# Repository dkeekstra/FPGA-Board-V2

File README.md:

# FPGA Board V2
## Key Features:
* Intel Cyclone 10 
* 16k logic elements
* Onboard usb programmer
* 3x 2.5khz to 200MHz programmable clock
* 4Mb on board configuration memory
* 40pin GPIO header
* USB OTG and HDMI connector
* RS485
* 8x User leds
* 5x User push buttons
* 4x User dip switches

By D. Keekstra

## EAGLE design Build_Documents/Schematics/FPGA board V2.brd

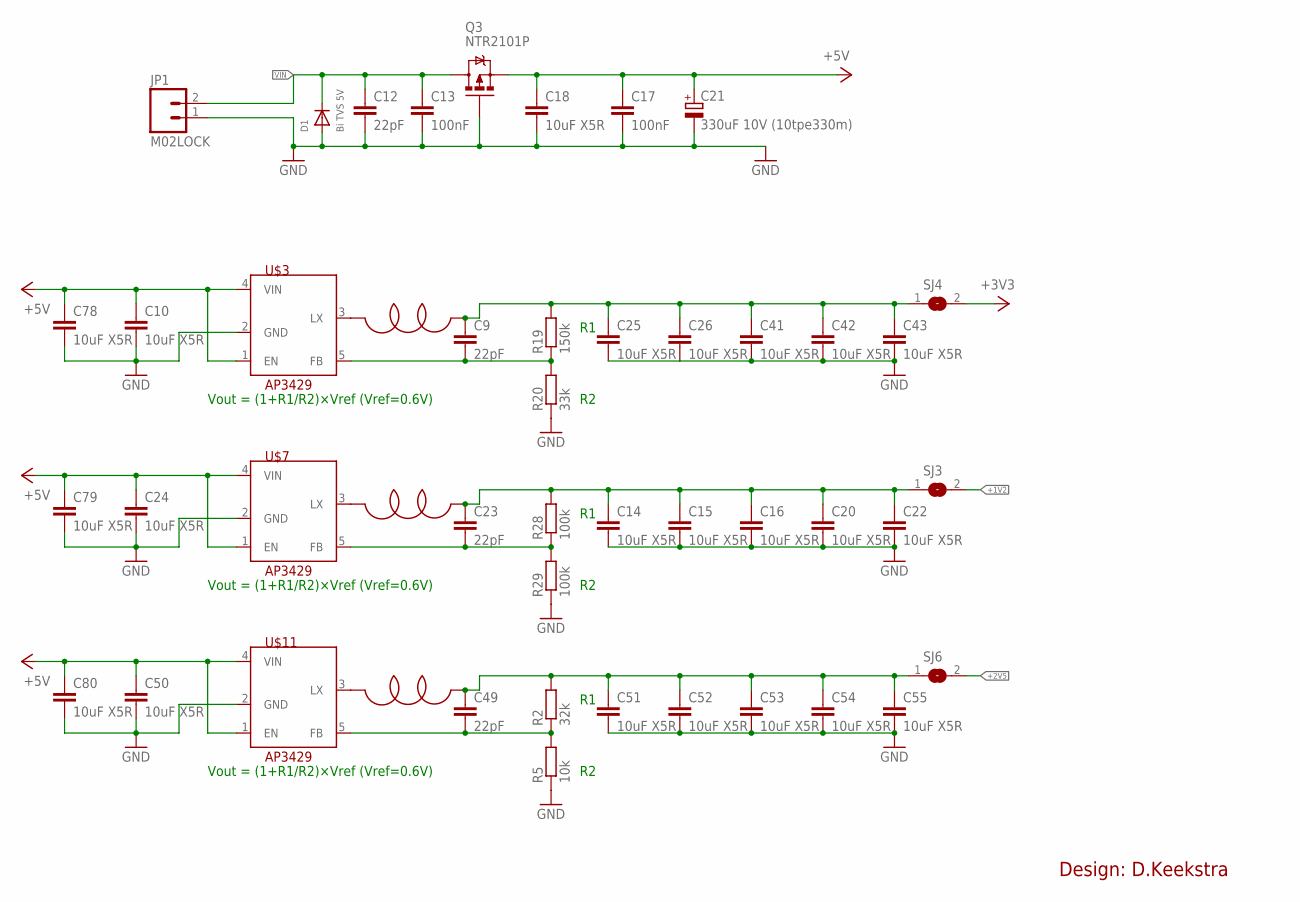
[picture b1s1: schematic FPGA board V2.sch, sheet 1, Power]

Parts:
C9, C12, C23, C49: 22pF; C0603
C10, C14, C15, C16, C18, C20, C22, C24, C25, C26, C41, C42, C43, C50, C51, C52, C53, C54, C55, C78, C79, C80: 10uF X5R; C0805K
C13, C17: 100nF; C0603
C21: 330uF 10V (10tpe330m); D/7343-31W
D1: Bi TVS 5V; SOD-523
JP1: M02LOCK; 1X02_LOCK
L2, L3, L4: 3.3uH 1.9A PWR; SLF7032T
Q3: NTR2101P; SOT23-3
R2: 32k; R0603
R5: 10k; R0603
R19: 150k; R0603
R20: 33k; R0603
R28, R29: 100k; R0603
SJ3, SJ4, SJ6: SJ
U$3, U$7, U$11: AP3429; TSOT-25

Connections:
+1V2: SJ3.2; also elsewhere on the board
+2V5: SJ6.2; also elsewhere on the board
+3V3: SJ4.2; also elsewhere on the board
+5V: C10.1, C17.1, C18.1, C21.+, C24.1, C50.1, C78.1, C79.1, C80.1, Q3.2 (S), U$3.1 (EN), U$3.4 (VIN), U$7.1 (EN), U$7.4 (VIN), U$11.1 (EN), U$11.4 (VIN); also elsewhere on the board
GND: C10.2, C12.2, C13.2, C14.2, C15.2, C16.2, C17.2, C18.2, C20.2, C21.-, C22.2, C24.2, C25.2, C26.2, C41.2, C42.2, C43.2, C50.2, C51.2, C52.2, C53.2, C54.2, C55.2, C78.2, C79.2, C80.2, D1.A, JP1.1, Q3.1 (G), R5.1, R20.1, R29.1, U$3.2 (GND), U$7.2 (GND), U$11.2 (GND); also elsewhere on the board
L2: C9.1, C25.1, C26.1, C41.1, C42.1, C43.1, L2.P$1, R19.2, SJ4.1
unnamed: L3.P$2, U$11.3 (LX)
unnamed: C49.1, C51.1, C52.1, C53.1, C54.1, C55.1, L3.P$1, R2.2, SJ6.1
unnamed: C49.2, R2.1, R5.2, U$11.5 (FB)
unnamed: C14.1, C15.1, C16.1, C20.1, C22.1, C23.1, L4.P$1, R28.2, SJ3.1
unnamed: C23.2, R28.1, R29.2, U$7.5 (FB)
unnamed: L2.P$2, U$3.3 (LX)
unnamed: C9.2, R19.1, R20.2, U$3.5 (FB)
unnamed: L4.P$2, U$7.3 (LX)
VIN: C12.1, C13.1, D1.K (C), JP1.2, Q3.3 (D); also elsewhere on the board

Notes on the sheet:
Vout = (1+R1/R2)×Vref (Vref=0.6V)
Design: D.Keekstra

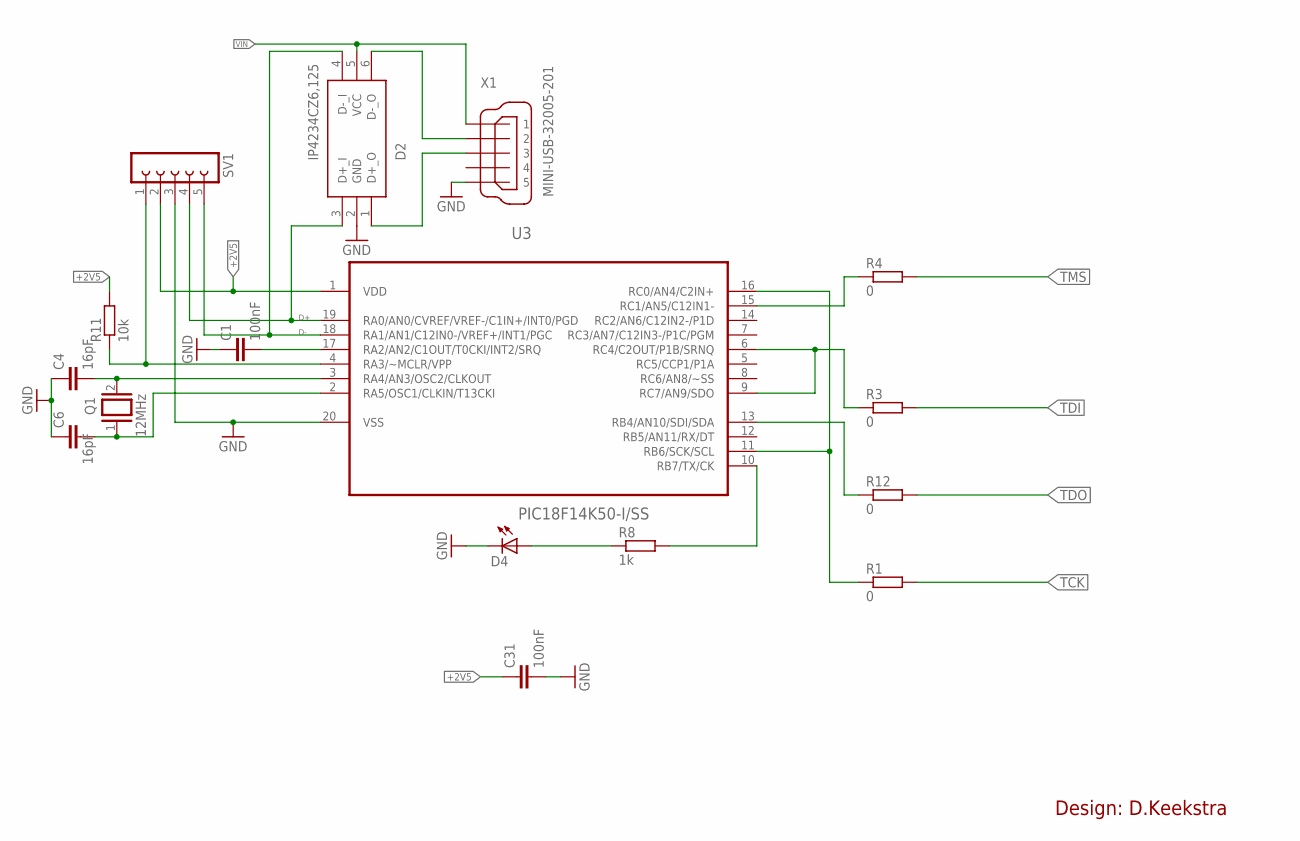
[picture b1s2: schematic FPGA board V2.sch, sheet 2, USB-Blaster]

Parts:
C1, C31: 100nF; C0603
C4, C6: 16pF; C0603
D2: IP4234CZ6,125; SOT95P275X110-6N
D4: LED0805; CHIPLED_0805
Q1: 12MHz; QS
R1, R3, R4, R12: 0; R0603
R8: 1k; R0603
R11: 10k; R0603
SV1: FE05-1
U3: PIC18F14K50-I/SS; SOP65P780X200-20N
X1: MINI-USB-32005-201; 32005-201

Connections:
+2V5: C31.1, R11.2, SV1.2, U3.1 (VDD); also elsewhere on the board
D+: D2.3 (D+_I), SV1.4, U3.19 (RA0/AN0/CVREF/VREF-/C1IN+/INT0/PGD)
D-: D2.4 (D-_I), SV1.5, U3.18 (RA1/AN1/C12IN0-/VREF+/INT1/PGC)
GND: C1.1, C4.1, C6.1, C31.2, D2.2 (GND), D4.C, SV1.3, U3.20 (VSS), X1.5; also elsewhere on the board
unnamed: R8.2, U3.10 (RB7/TX/CK)
unnamed: D4.A, R8.1
unnamed: R1.1, U3.11 (RB6/SCK/SCL), U3.16 (RC0/AN4/C2IN+)
unnamed: C1.2, U3.17 (RA2/AN2/C1OUT/T0CKI/INT2/SRQ)
unnamed: R4.1, U3.15 (RC1/AN5/C12IN1-)
unnamed: R11.1, SV1.1, U3.4 (RA3/~MCLR/VPP)
unnamed: R3.1, U3.6 (RC4/C2OUT/P1B/SRNQ), U3.9 (RC7/AN9/SDO)
unnamed: D2.1 (D+_O), X1.3
unnamed: R12.1, U3.13 (RB4/AN10/SDI/SDA)
unnamed: D2.6 (D-_O), X1.2
unnamed: C4.2, Q1.2, U3.3 (RA4/AN3/OSC2/CLKOUT)
unnamed: C6.2, Q1.1, U3.2 (RA5/OSC1/CLKIN/T13CKI)
TCK: R1.2; also elsewhere on the board
TDI: R3.2; also elsewhere on the board
TDO: R12.2; also elsewhere on the board
TMS: R4.2; also elsewhere on the board
VIN: D2.5 (VCC), X1.1; also elsewhere on the board

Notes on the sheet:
Design: D.Keekstra

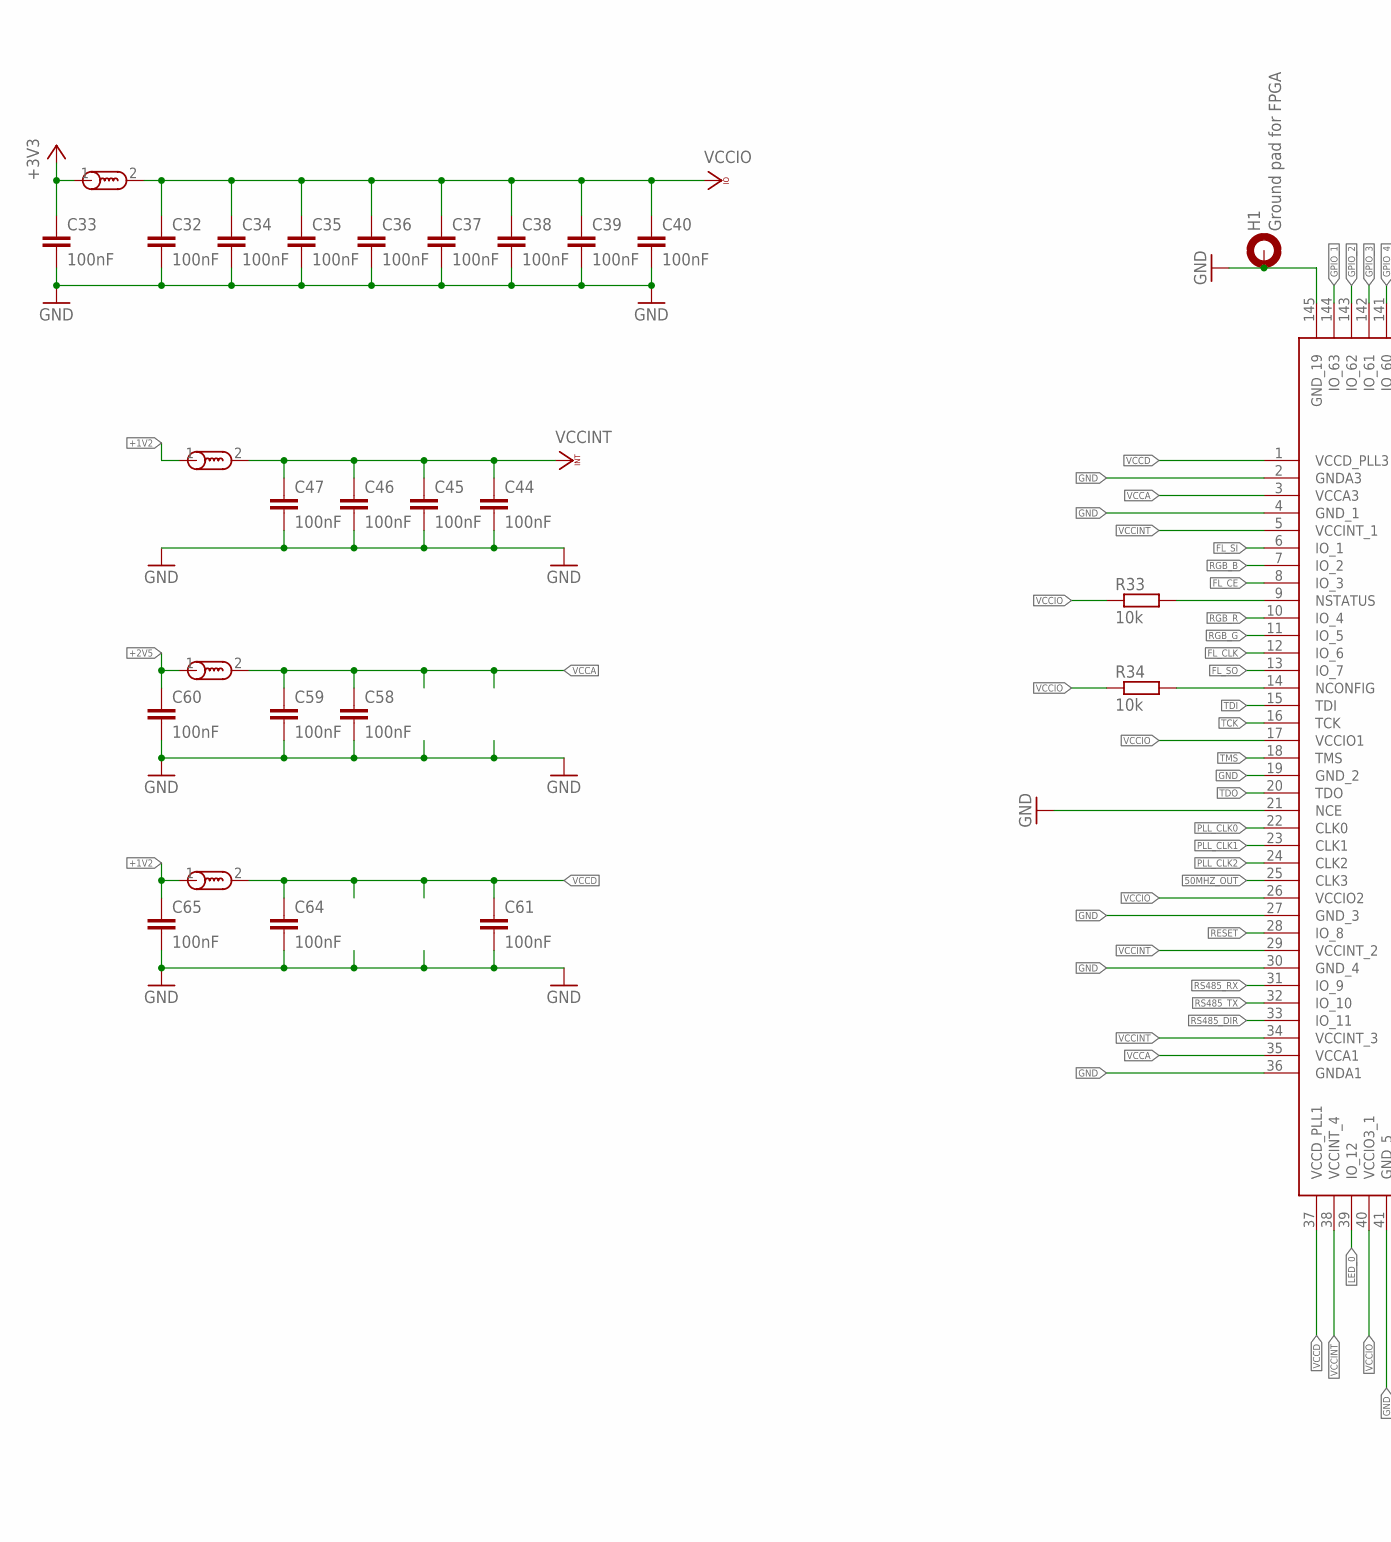
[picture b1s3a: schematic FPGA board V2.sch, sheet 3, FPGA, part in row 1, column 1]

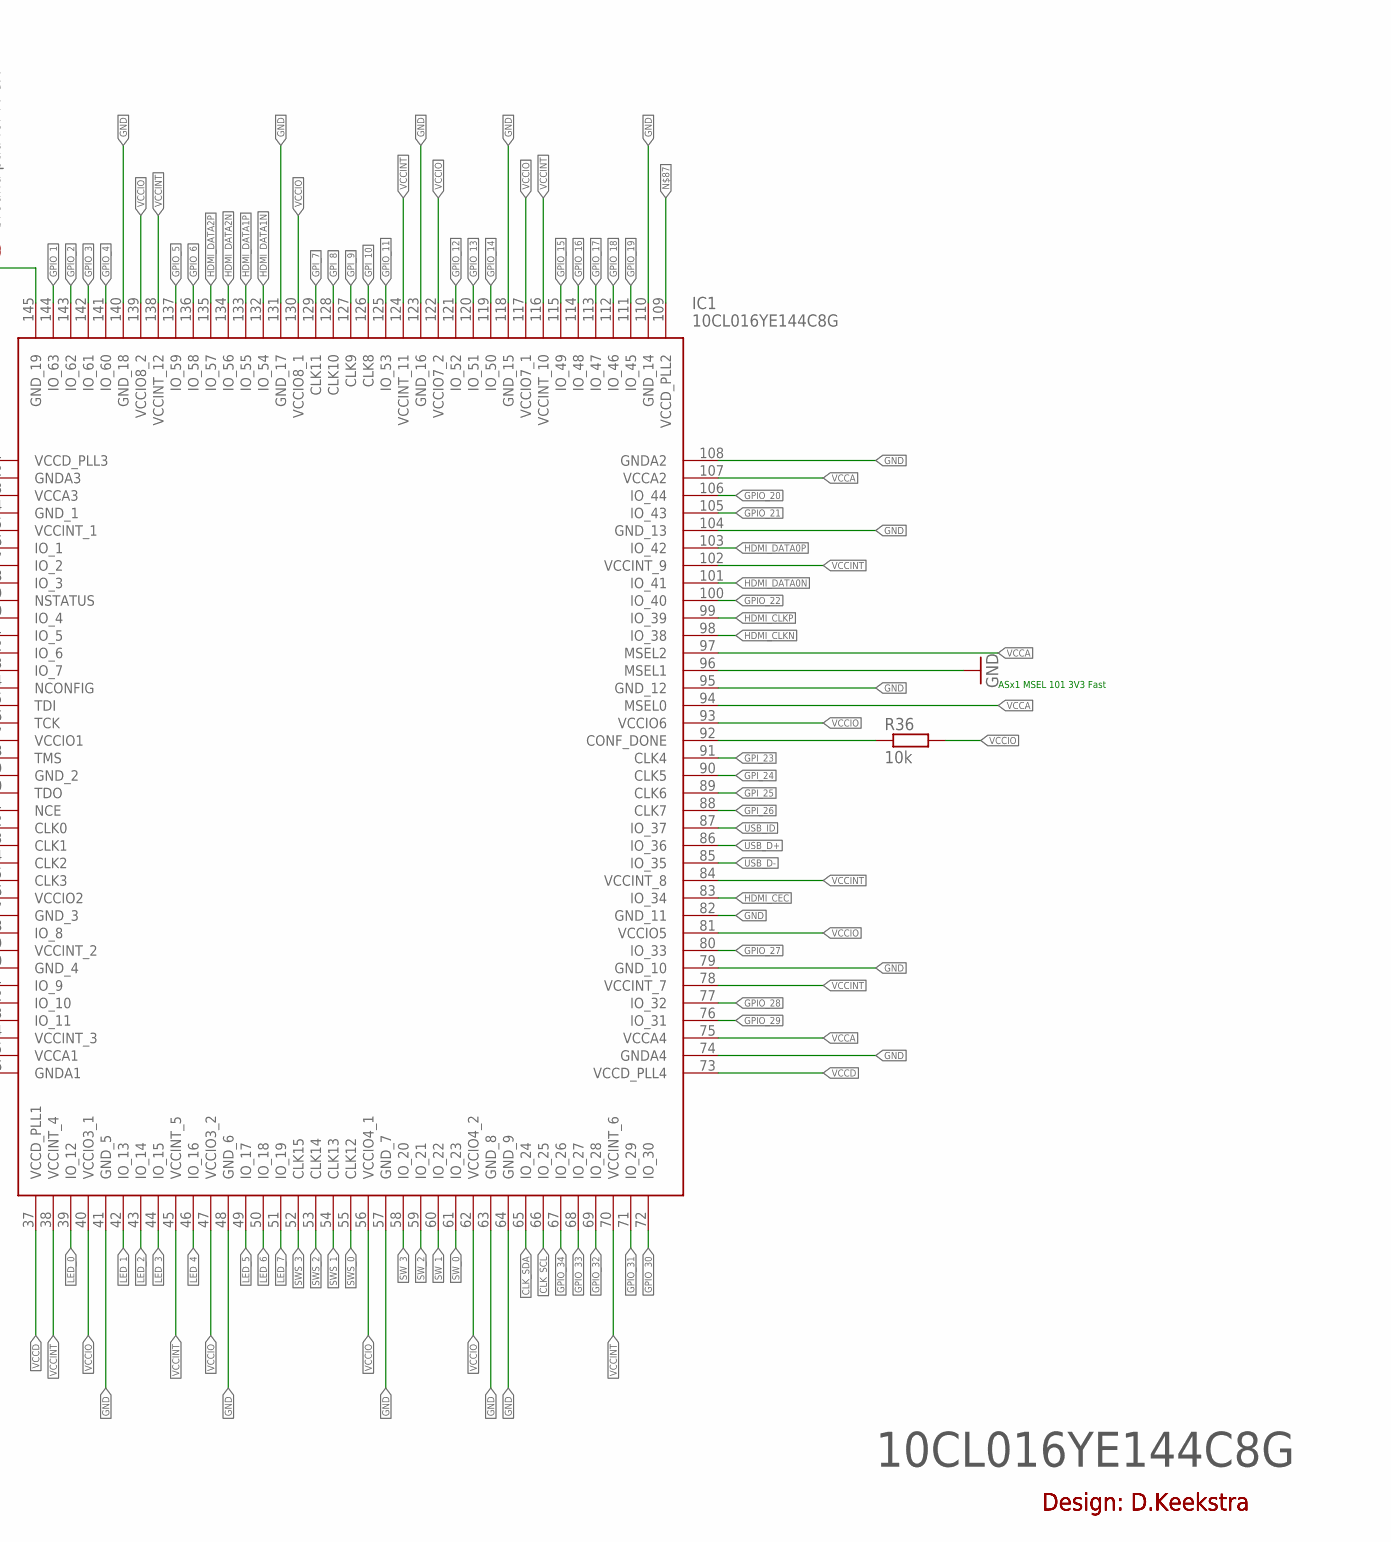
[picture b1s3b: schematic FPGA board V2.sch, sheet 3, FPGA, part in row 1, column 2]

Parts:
B1, B2, B3, B4: B-EU; C0603
C32, C33, C34, C35, C36, C37, C38, C39, C40, C44, C45, C46, C47, C58, C59, C60, C61, C64, C65: 100nF; C0603
H1: Ground pad for FPGA; 2,8-PAD
IC1: 10CL016YE144C8G; QFP50P2200X2200X165-145N
R33, R34, R36: 10k; R0603

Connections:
50MHZ_OUT: IC1.25 (CLK3); also elsewhere on the board
+1V2: B2.1, B4.1, C65.1; also elsewhere on the board
+2V5: B3.1, C60.1; also elsewhere on the board
+3V3: B1.1, C33.1; also elsewhere on the board
CLK_SCL: IC1.66 (IO_25); also elsewhere on the board
CLK_SDA: IC1.65 (IO_24); also elsewhere on the board
FL_CE: IC1.8 (IO_3); also elsewhere on the board
FL_CLK: IC1.12 (IO_6); also elsewhere on the board
FL_SI: IC1.6 (IO_1); also elsewhere on the board
FL_SO: IC1.13 (IO_7); also elsewhere on the board
GND: C32.2, C33.2, C34.2, C35.2, C36.2, C37.2, C38.2, C39.2, C40.2, C44.2, C45.2, C46.2, C47.2, C58.2, C59.2, C60.2, C61.2, C64.2, C65.2, H1.B2,8, IC1.2 (GNDA3), IC1.4 (GND_1), IC1.19 (GND_2), IC1.21 (NCE), IC1.27 (GND_3), IC1.30 (GND_4), IC1.36 (GNDA1), IC1.41 (GND_5), IC1.48 (GND_6), IC1.57 (GND_7), IC1.63 (GND_8), IC1.64 (GND_9), IC1.74 (GNDA4), IC1.79 (GND_10), IC1.82 (GND_11), IC1.95 (GND_12), IC1.96 (MSEL1), IC1.104 (GND_13), IC1.108 (GNDA2), IC1.110 (GND_14), IC1.118 (GND_15), IC1.123 (GND_16), IC1.131 (GND_17), IC1.140 (GND_18), IC1.145 (GND_19); also elsewhere on the board
GPIO_1: IC1.144 (IO_63); also elsewhere on the board
GPIO_2: IC1.143 (IO_62); also elsewhere on the board
GPIO_3: IC1.142 (IO_61); also elsewhere on the board
GPIO_4: IC1.141 (IO_60); also elsewhere on the board
GPIO_5: IC1.137 (IO_59); also elsewhere on the board
GPIO_6: IC1.136 (IO_58); also elsewhere on the board
GPIO_11: IC1.125 (IO_53); also elsewhere on the board
GPIO_12: IC1.121 (IO_52); also elsewhere on the board
GPIO_13: IC1.120 (IO_51); also elsewhere on the board
GPIO_14: IC1.119 (IO_50); also elsewhere on the board
GPIO_15: IC1.115 (IO_49); also elsewhere on the board
GPIO_16: IC1.114 (IO_48); also elsewhere on the board
GPIO_17: IC1.113 (IO_47); also elsewhere on the board
GPIO_18: IC1.112 (IO_46); also elsewhere on the board
GPIO_19: IC1.111 (IO_45); also elsewhere on the board
GPIO_20: IC1.106 (IO_44); also elsewhere on the board
GPIO_21: IC1.105 (IO_43); also elsewhere on the board
GPIO_22: IC1.100 (IO_40); also elsewhere on the board
GPIO_27: IC1.80 (IO_33); also elsewhere on the board
GPIO_28: IC1.77 (IO_32); also elsewhere on the board
GPIO_29: IC1.76 (IO_31); also elsewhere on the board
GPIO_30: IC1.72 (IO_30); also elsewhere on the board
GPIO_31: IC1.71 (IO_29); also elsewhere on the board
GPIO_32: IC1.69 (IO_28); also elsewhere on the board
GPIO_33: IC1.68 (IO_27); also elsewhere on the board
GPIO_34: IC1.67 (IO_26); also elsewhere on the board
GPI_7: IC1.129 (CLK11); also elsewhere on the board
GPI_8: IC1.128 (CLK10); also elsewhere on the board
GPI_9: IC1.127 (CLK9); also elsewhere on the board
GPI_10: IC1.126 (CLK8); also elsewhere on the board
GPI_23: IC1.91 (CLK4); also elsewhere on the board
GPI_24: IC1.90 (CLK5); also elsewhere on the board
GPI_25: IC1.89 (CLK6); also elsewhere on the board
GPI_26: IC1.88 (CLK7); also elsewhere on the board
HDMI_CEC: IC1.83 (IO_34); also elsewhere on the board
HDMI_CLKN: IC1.98 (IO_38); also elsewhere on the board
HDMI_CLKP: IC1.99 (IO_39); also elsewhere on the board
HDMI_DATA0N: IC1.101 (IO_41); also elsewhere on the board
HDMI_DATA0P: IC1.103 (IO_42); also elsewhere on the board
HDMI_DATA1N: IC1.132 (IO_54); also elsewhere on the board
HDMI_DATA1P: IC1.133 (IO_55); also elsewhere on the board
HDMI_DATA2N: IC1.134 (IO_56); also elsewhere on the board
HDMI_DATA2P: IC1.135 (IO_57); also elsewhere on the board
LED_0: IC1.39 (IO_12); also elsewhere on the board
LED_1: IC1.42 (IO_13); also elsewhere on the board
LED_2: IC1.43 (IO_14); also elsewhere on the board
LED_3: IC1.44 (IO_15); also elsewhere on the board
LED_4: IC1.46 (IO_16); also elsewhere on the board
LED_5: IC1.49 (IO_17); also elsewhere on the board
LED_6: IC1.50 (IO_18); also elsewhere on the board
LED_7: IC1.51 (IO_19); also elsewhere on the board
unnamed: IC1.9 (NSTATUS), R33.2
unnamed: IC1.14 (NCONFIG), R34.2
unnamed: IC1.92 (CONF_DONE), R36.1
PLL_CLK0: IC1.22 (CLK0); also elsewhere on the board
PLL_CLK1: IC1.23 (CLK1); also elsewhere on the board
PLL_CLK2: IC1.24 (CLK2); also elsewhere on the board
RESET: IC1.28 (IO_8); also elsewhere on the board
RGB_B: IC1.7 (IO_2); also elsewhere on the board
RGB_G: IC1.11 (IO_5); also elsewhere on the board
RGB_R: IC1.10 (IO_4); also elsewhere on the board
RS485_DIR: IC1.33 (IO_11); also elsewhere on the board
RS485_RX: IC1.31 (IO_9); also elsewhere on the board
RS485_TX: IC1.32 (IO_10); also elsewhere on the board
SWS_0: IC1.55 (CLK12); also elsewhere on the board
SWS_1: IC1.54 (CLK13); also elsewhere on the board
SWS_2: IC1.53 (CLK14); also elsewhere on the board
SWS_3: IC1.52 (CLK15); also elsewhere on the board
SW_0: IC1.61 (IO_23); also elsewhere on the board
SW_1: IC1.60 (IO_22); also elsewhere on the board
SW_2: IC1.59 (IO_21); also elsewhere on the board
SW_3: IC1.58 (IO_20); also elsewhere on the board
TCK: IC1.16 (TCK); also elsewhere on the board
TDI: IC1.15 (TDI); also elsewhere on the board
TDO: IC1.20 (TDO); also elsewhere on the board
TMS: IC1.18 (TMS); also elsewhere on the board
USB_D+: IC1.86 (IO_36); also elsewhere on the board
USB_D-: IC1.85 (IO_35); also elsewhere on the board
USB_ID: IC1.87 (IO_37); also elsewhere on the board
VCCA: B3.2, C58.1, C59.1, IC1.3 (VCCA3), IC1.35 (VCCA1), IC1.75 (VCCA4), IC1.94 (MSEL0), IC1.97 (MSEL2), IC1.107 (VCCA2)
VCCD: B4.2, C61.1, C64.1, IC1.1 (VCCD_PLL3), IC1.37 (VCCD_PLL1), IC1.73 (VCCD_PLL4)
VCCINT: B2.2, C44.1, C45.1, C46.1, C47.1, IC1.5 (VCCINT_1), IC1.29 (VCCINT_2), IC1.34 (VCCINT_3), IC1.38 (VCCINT_4), IC1.45 (VCCINT_5), IC1.70 (VCCINT_6), IC1.78 (VCCINT_7), IC1.84 (VCCINT_8), IC1.102 (VCCINT_9), IC1.116 (VCCINT_10), IC1.124 (VCCINT_11), IC1.138 (VCCINT_12)
VCCIO: B1.2, C32.1, C34.1, C35.1, C36.1, C37.1, C38.1, C39.1, C40.1, IC1.17 (VCCIO1), IC1.26 (VCCIO2), IC1.40 (VCCIO3_1), IC1.47 (VCCIO3_2), IC1.56 (VCCIO4_1), IC1.62 (VCCIO4_2), IC1.81 (VCCIO5), IC1.93 (VCCIO6), IC1.117 (VCCIO7_1), IC1.122 (VCCIO7_2), IC1.130 (VCCIO8_1), IC1.139 (VCCIO8_2), R33.1, R34.1, R36.2

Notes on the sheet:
10CL016YE144C8G
ASx1 MSEL 101 3V3 Fast
Design: D.Keekstra

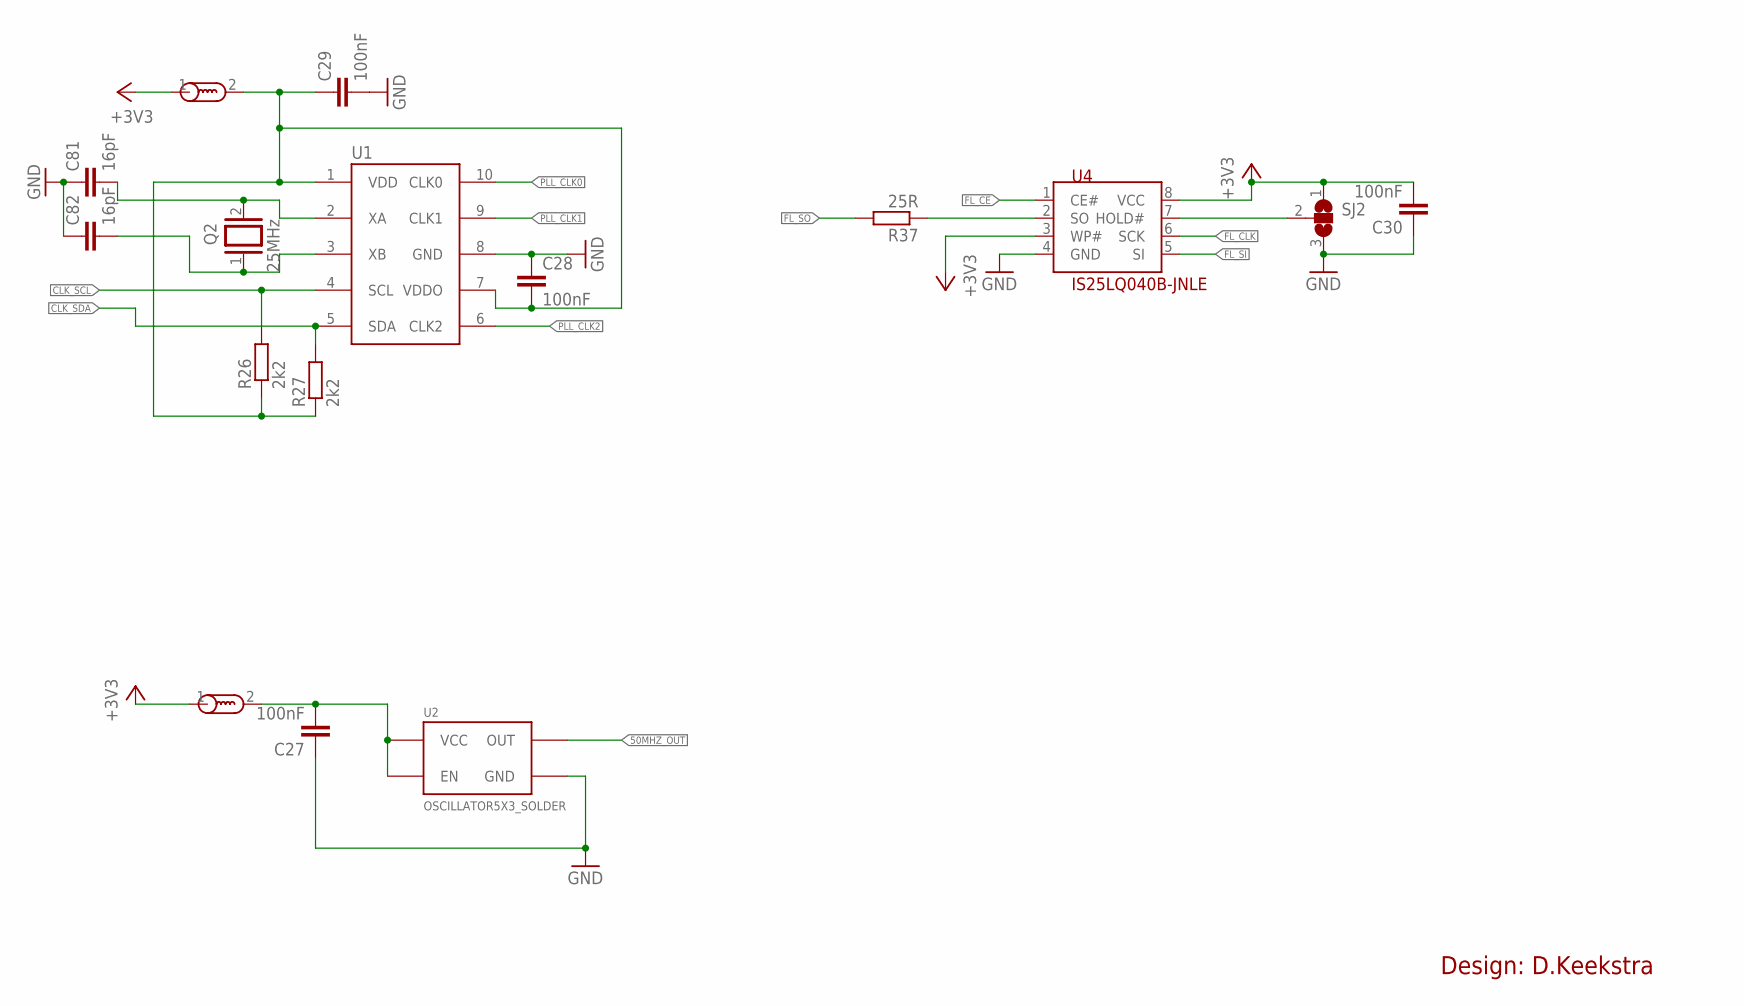
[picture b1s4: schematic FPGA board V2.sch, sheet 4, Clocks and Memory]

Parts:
B5, B6: B-EU; C0603
C27, C28, C29, C30: 100nF; C0603
C81, C82: 16pF; C0603
Q2: 25MHz; QS
R26, R27: 2k2; R0603
R37: 25R; R0603
SJ2: SJ2W; SJ_2
U1: SI5351A_CLOCK_GEN; MSOP-10
U2: OSCILLATOR5X3_SOLDER; CRYSTAL-SMD-5X3_SOLDER
U4: IS25LQ040B-JNLE; SOIC8

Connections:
50MHZ_OUT: U2.3 (OUT); also elsewhere on the board
+3V3: B5.1, B6.1, C30.2, SJ2.1, U4.3 (WP#), U4.8 (VCC); also elsewhere on the board
CLK_SCL: R26.2, U1.4 (SCL); also elsewhere on the board
CLK_SDA: R27.2, U1.5 (SDA); also elsewhere on the board
FL_CE: U4.1 (CE#); also elsewhere on the board
FL_CLK: U4.6 (SCK); also elsewhere on the board
FL_SI: U4.5 (SI); also elsewhere on the board
FL_SO: R37.2; also elsewhere on the board
GND: C27.1, C28.1, C29.2, C30.1, C81.1, C82.1, SJ2.3, U1.8 (GND), U2.2 (GND), U4.4 (GND); also elsewhere on the board
unnamed: C82.2, Q2.1, U1.3 (XB)
unnamed: C81.2, Q2.2, U1.2 (XA)
unnamed: SJ2.2, U4.7 (HOLD#)
unnamed: B6.2, C28.2, C29.1, R26.1, R27.1, U1.1 (VDD), U1.7 (VDDO)
unnamed: B5.2, C27.2, U2.1 (EN), U2.4 (VCC)
PLL_CLK0: U1.10 (CLK0); also elsewhere on the board
PLL_CLK1: U1.9 (CLK1); also elsewhere on the board
PLL_CLK2: U1.6 (CLK2); also elsewhere on the board
SO: R37.1, U4.2 (SO)

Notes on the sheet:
Design: D.Keekstra

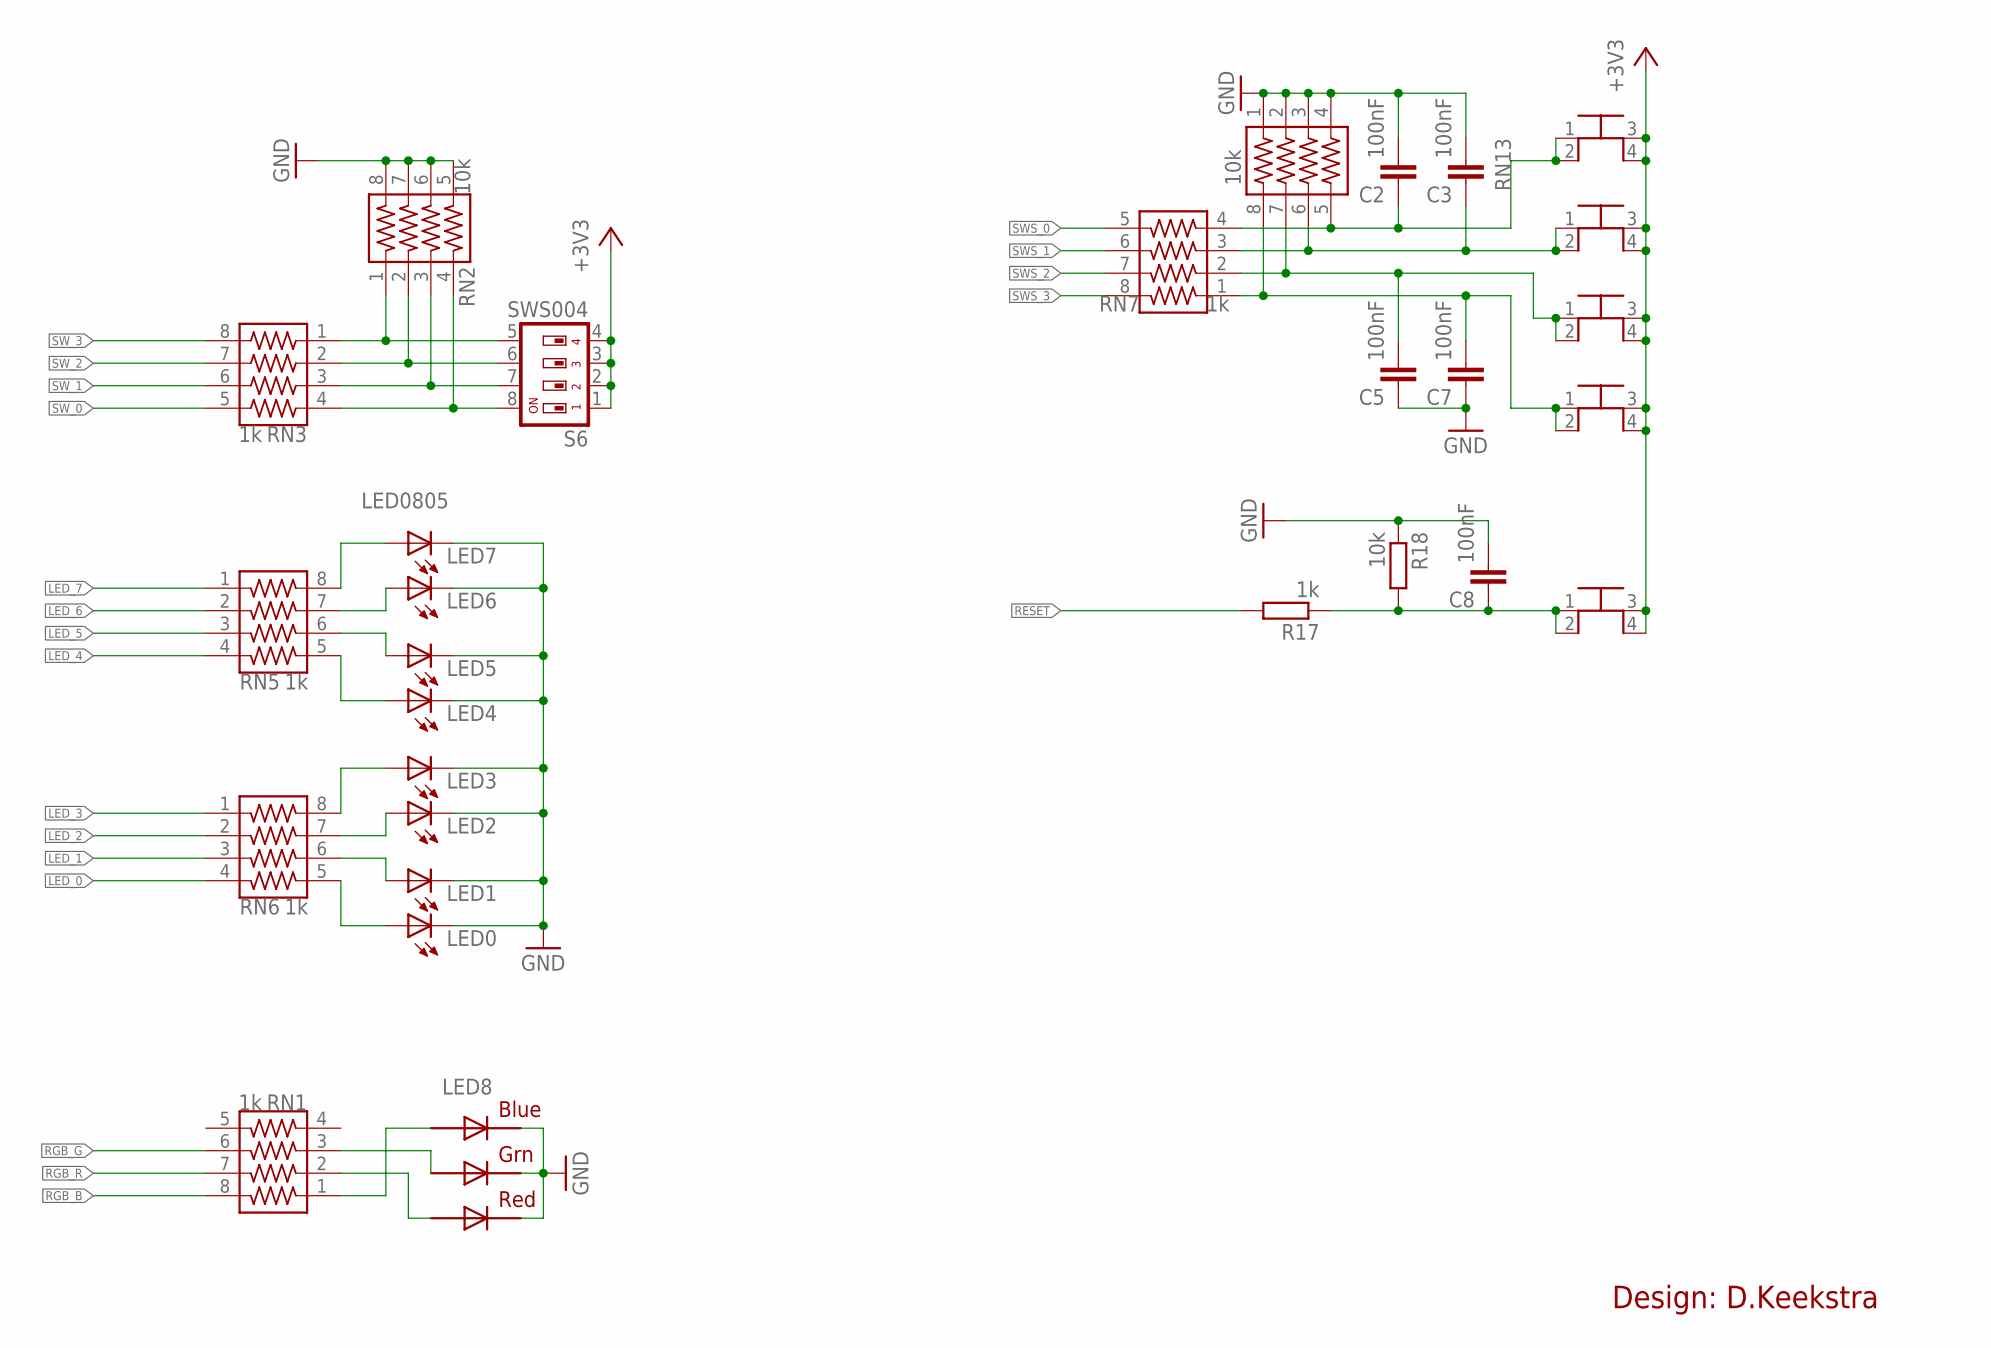
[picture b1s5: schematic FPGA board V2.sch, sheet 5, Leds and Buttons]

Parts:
C2, C3, C5, C7, C8: 100nF; C0603
LED0, LED1, LED2, LED3, LED4, LED5, LED6, LED7: LED0805; CHIPLED_0805
LED8: RGBLED5050
R17: 1k; R0603
R18: 10k; R0603
RN1, RN3, RN5, RN6, RN7: 1k; 744-8NS
RN2, RN13: 10k; 744-8NS
S1, S2, S3, S4, S5: SKQGADE010; SKQGAKE010
S6: SWS004; SMS-004

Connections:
+3V3: S1.3, S1.4, S2.3, S2.4, S3.3, S3.4, S4.3, S4.4, S5.3, S5.4, S6.1, S6.2, S6.3, S6.4; also elsewhere on the board
GND: C2.2, C3.2, C5.1, C7.1, C8.2, LED0.C, LED1.C, LED2.C, LED3.C, LED4.C, LED5.C, LED6.C, LED7.C, LED8.4 (BLUE_C), LED8.5 (RED_C), LED8.6 (GREEN_C), R18.1, RN2.5, RN2.6, RN2.7, RN2.8, RN13.1, RN13.2, RN13.3, RN13.4; also elsewhere on the board
LED_0: RN6.4; also elsewhere on the board
LED_1: RN6.3; also elsewhere on the board
LED_2: RN6.2; also elsewhere on the board
LED_3: RN6.1; also elsewhere on the board
LED_4: RN5.4; also elsewhere on the board
LED_5: RN5.3; also elsewhere on the board
LED_6: RN5.2; also elsewhere on the board
LED_7: RN5.1; also elsewhere on the board
unnamed: RN2.3, RN3.3, S6.7
unnamed: RN2.1, RN3.1, S6.5
unnamed: RN2.2, RN3.2, S6.6
unnamed: RN2.4, RN3.4, S6.8
unnamed: LED7.A, RN5.8
unnamed: LED6.A, RN5.7
unnamed: LED5.A, RN5.6
unnamed: LED4.A, RN5.5
unnamed: LED3.A, RN6.8
unnamed: LED2.A, RN6.7
unnamed: LED1.A, RN6.6
unnamed: LED0.A, RN6.5
unnamed: LED8.1 (GREEN_A), RN1.3
unnamed: LED8.2 (RED_A), RN1.2
unnamed: LED8.3 (BLUE_A), RN1.1
unnamed: C2.1, RN7.4, RN13.5, S4.1, S4.2
unnamed: C3.1, RN7.3, RN13.6, S3.1, S3.2
unnamed: C5.2, RN7.2, RN13.7, S2.1, S2.2
unnamed: C7.2, RN7.1, RN13.8, S1.1, S1.2
unnamed: C8.1, R17.1, R18.2, S5.1, S5.2
RESET: R17.2; also elsewhere on the board
RGB_B: RN1.8; also elsewhere on the board
RGB_G: RN1.6; also elsewhere on the board
RGB_R: RN1.7; also elsewhere on the board
SWS_0: RN7.5; also elsewhere on the board
SWS_1: RN7.6; also elsewhere on the board
SWS_2: RN7.7; also elsewhere on the board
SWS_3: RN7.8; also elsewhere on the board
SW_0: RN3.5; also elsewhere on the board
SW_1: RN3.6; also elsewhere on the board
SW_2: RN3.7; also elsewhere on the board
SW_3: RN3.8; also elsewhere on the board

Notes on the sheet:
Design: D.Keekstra

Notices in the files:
parts and their libraries:
SparkFun-DiscreteSemi: Licensing: Creative Commons ShareAlike 4.0 International - https://creativecommons.org/licenses/by-sa/4.0
resistor-array: Copyright (C) 2008, Bob Starr
